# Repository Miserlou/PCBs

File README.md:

# Black Death PCBs

Kosmo circuits/panels by me. Mostly hacks of other people's work.

USE THESE AT YOUR OWN RISK, SOME HAVE MAJOR BUGS! You probably want to talk to me before making these.

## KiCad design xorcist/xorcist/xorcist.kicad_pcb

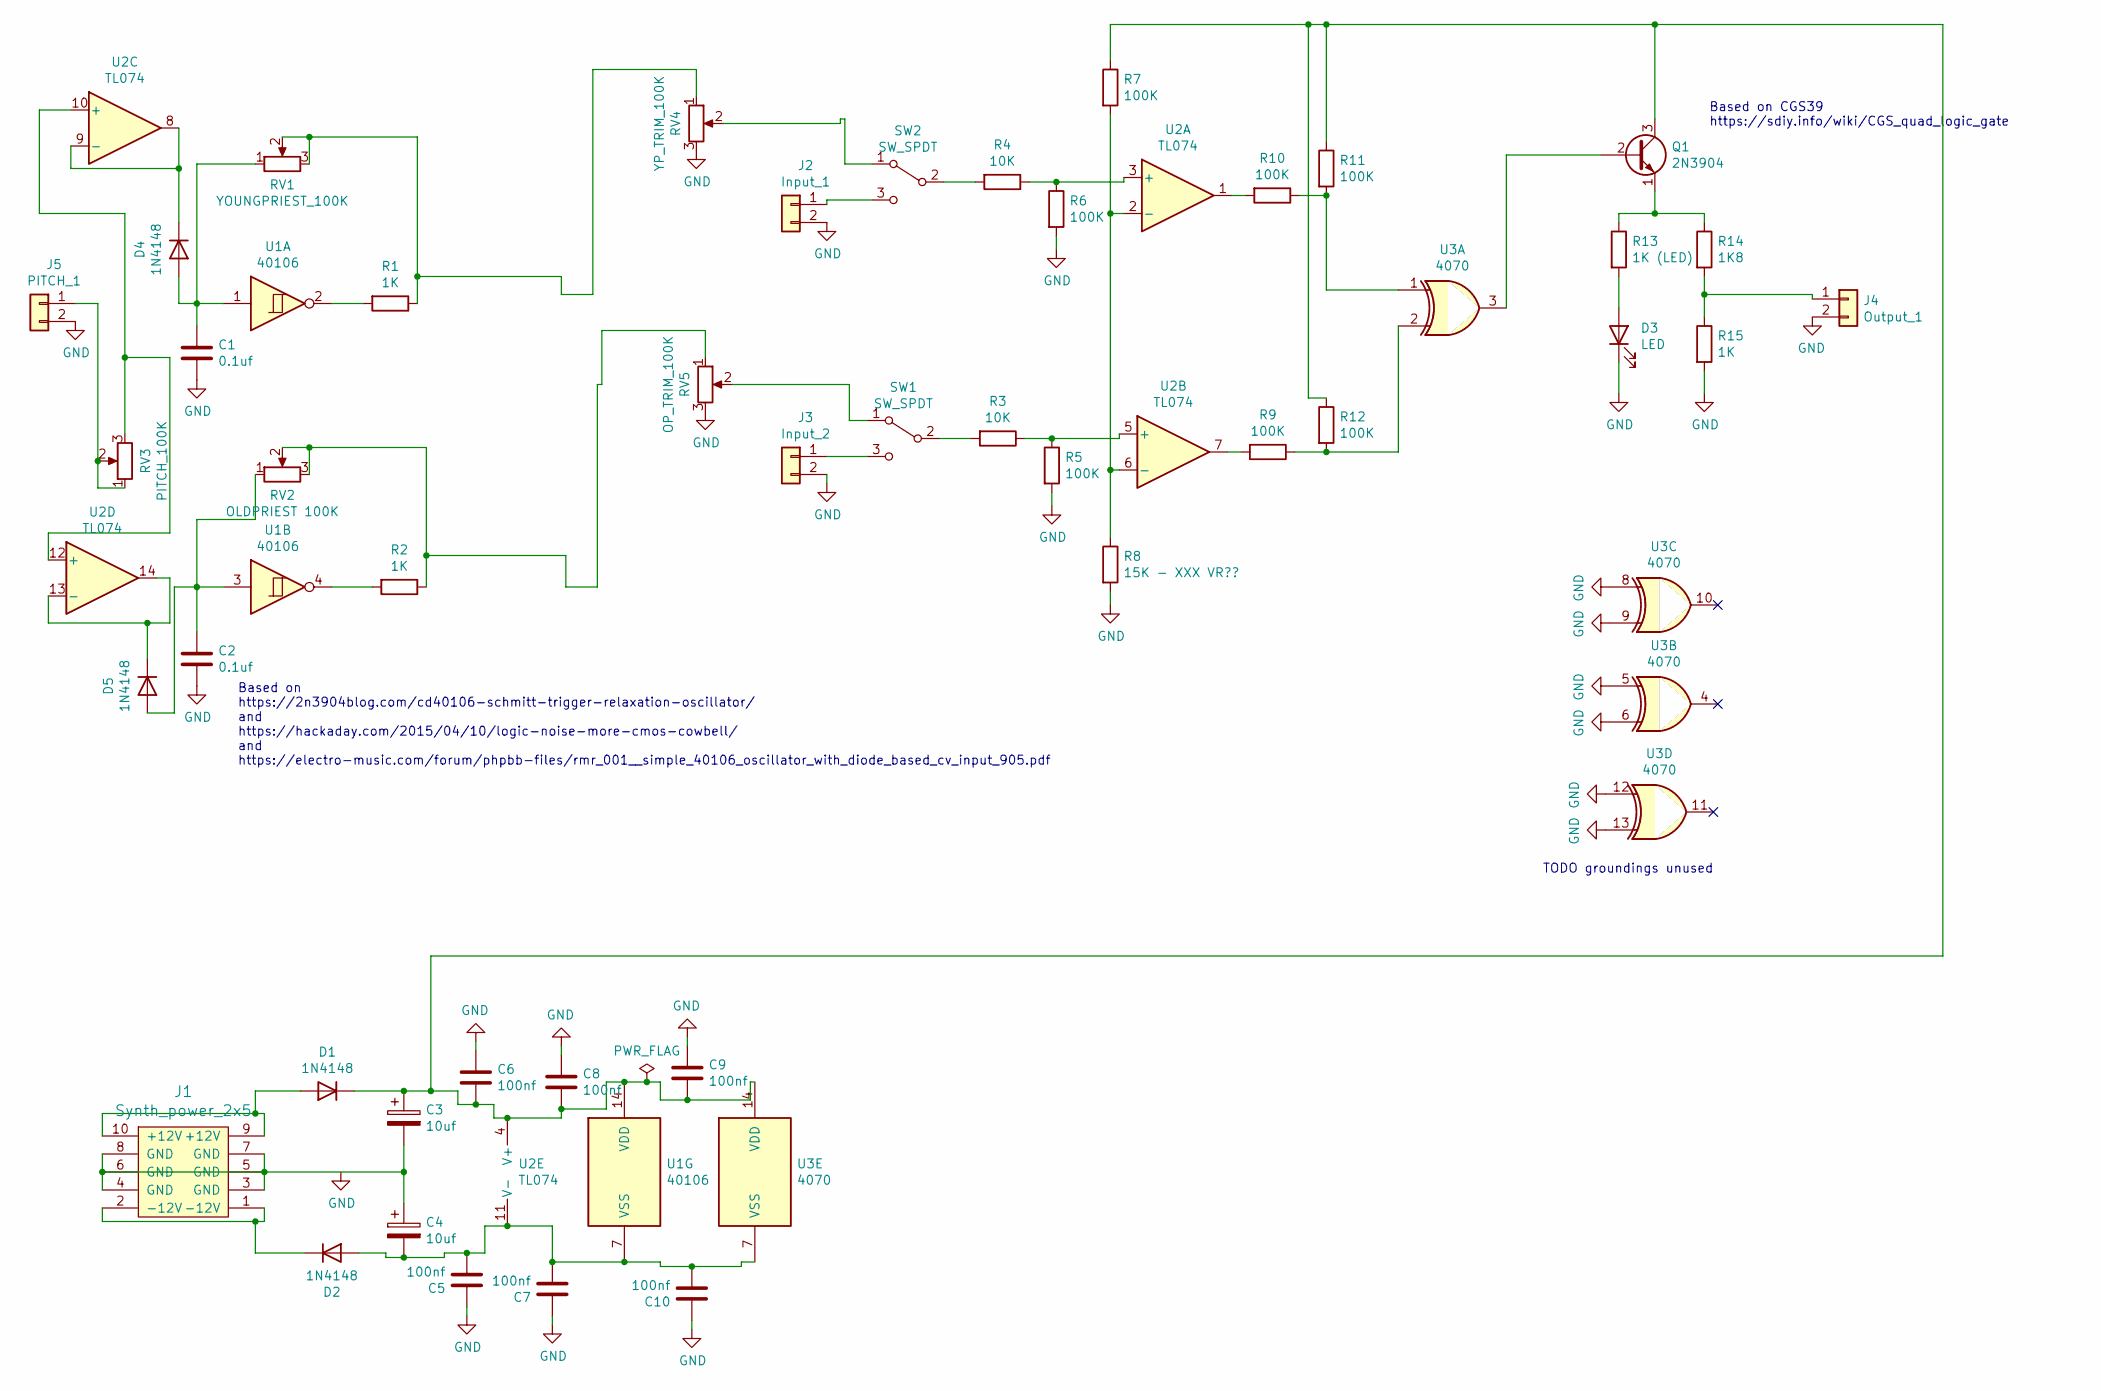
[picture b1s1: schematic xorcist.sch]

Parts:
C1, C2: 0.1uf; C_Disc_D3.0mm_W1.6mm_P2.50mm
C3, C4: 10uf; CP_Radial_D6.3mm_P2.50mm
C5, C6, C7, C8, C9, C10: 100nf; C_Disc_D3.0mm_W1.6mm_P2.50mm
D1, D2, D4, D5: 1N4148; D_DO-35_SOD27_P7.62mm_Horizontal
D3: LED; LED_D5.0mm
J1: Synth_power_2x5; Power_Header
J2: Input_1; Molex_KK-254_AE-6410-02A_1x02_P2.54mm_Vertical
J3: Input_2; Molex_KK-254_AE-6410-02A_1x02_P2.54mm_Vertical
J4: Output_1; Molex_KK-254_AE-6410-02A_1x02_P2.54mm_Vertical
J5: PITCH_1; Molex_KK-254_AE-6410-02A_1x02_P2.54mm_Vertical
Q1: 2N3904; TO-92_Inline_Wide
R1, R2, R15: 1K; R_Axial_DIN0207_L6.3mm_D2.5mm_P10.16mm_Horizontal
R3, R4: 10K; R_Axial_DIN0207_L6.3mm_D2.5mm_P10.16mm_Horizontal
R5, R6, R7, R9, R10, R11, R12: 100K; R_Axial_DIN0207_L6.3mm_D2.5mm_P10.16mm_Horizontal
R8: 15K - XXX VR??; R_Axial_DIN0207_L6.3mm_D2.5mm_P10.16mm_Horizontal
R13: 1K (LED); R_Axial_DIN0207_L6.3mm_D2.5mm_P10.16mm_Horizontal
R14: 1K8; R_Axial_DIN0207_L6.3mm_D2.5mm_P10.16mm_Horizontal
RV1: YOUNGPRIEST_100K; Potentiometer_Alpha_RD901F-40-00D_Single_Vertical_CircularH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
RV2: OLDPRIEST 100K; Potentiometer_Alpha_RD901F-40-00D_Single_Vertical_CircularH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
RV3: PITCH_100K; Potentiometer_Alpha_RD901F-40-00D_Single_Vertical_CircularH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
RV4: YP_TRIM_100K; Potentiometer_Bourns_3296W_Vertical_standard
RV5: OP_TRIM_100K; Potentiometer_Bourns_3296W_Vertical_standard
SW1, SW2: SW_SPDT; SPDT-toggle-switch-1M-series
U1: 40106; DIP-14_W7.62mm_Socket_LongPads
U2: TL074; DIP-16_W7.62mm_Socket_LongPads
U3: 4070; DIP-14_W7.62mm_Socket_LongPads

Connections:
unnamed: C1.1, D4.2 (A), RV1.1, U1.1
unnamed: C2.1, D5.2 (A), RV2.1, U1.3
unnamed: C3.1, C6.2, C8.2, C9.2, D1.1 (K), Q1.3 (C), R7.1, R11.1, R12.1, U1.14 (VDD), U2.4 (V+), U3.14 (VDD)
unnamed: C4.2, C5.2, C7.2, C10.2, D2.2 (A), U1.7 (VSS), U2.11 (V-), U3.7 (VSS)
unnamed: D1.2 (A), J1.9 (+12V), J1.10 (+12V)
unnamed: D2.1 (K), J1.1 (-12V), J1.2 (-12V)
unnamed: D3.2 (A), R13.2
unnamed: D4.1 (K), U2.8, U2.9 (-)
unnamed: D5.1 (K), U2.13 (-), U2.14
unnamed 9: J2.1, SW2.3 (C); also elsewhere on the board
unnamed 10: J3.1, SW1.3 (C); also elsewhere on the board
unnamed 11: J4.1, R14.2, R15.1; also elsewhere on the board
unnamed 12: J5.1, RV3.1, RV3.2; also elsewhere on the board
unnamed: Q1.1 (E), R13.1, R14.1
unnamed: Q1.2 (B), U3.3
unnamed: R1.1, RV1.2, RV1.3, RV4.1
unnamed: R1.2, U1.2
unnamed: R2.1, RV2.2, RV2.3, RV5.1
unnamed: R2.2, U1.4
unnamed: R3.1, R5.1, U2.5 (+)
unnamed: R3.2, SW1.2 (B)
unnamed: R4.1, R6.1, U2.3 (+)
unnamed: R4.2, SW2.2 (B)
unnamed: R7.2, R8.1, U2.2 (-), U2.6 (-)
unnamed: R9.2, U2.7
unnamed: R10.1, R11.2, U3.1
unnamed: R10.2, U2.1
unnamed: R9.1, R12.2, U3.2
unnamed: RV3.3, U2.10 (+), U2.12 (+)
unnamed: RV4.2, SW2.1 (A)
unnamed: RV5.2, SW1.1 (A)

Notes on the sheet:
Based on CGS39 https://sdiy.info/wiki/CGS_quad_logic_gate
Based on https://2n3904blog.com/cd40106-schmitt-trigger-relaxation-oscillator/ and https://hackaday.com/2015/04/10/logic-noise-more-cmos-cowbell/ and https://electro-music.com/forum/phpbb-files/rmr_001__simple_40106_oscillator_with_diode_based_cv_input_905.pdf
TODO groundings unused

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
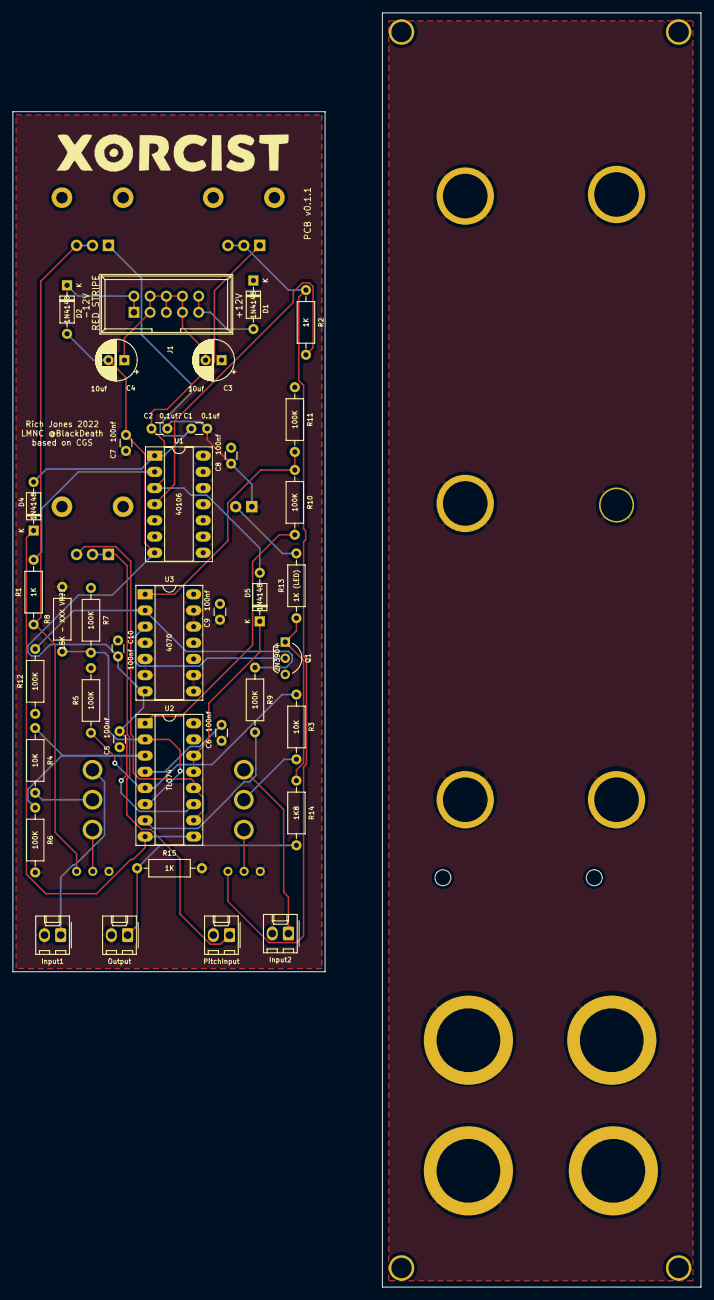
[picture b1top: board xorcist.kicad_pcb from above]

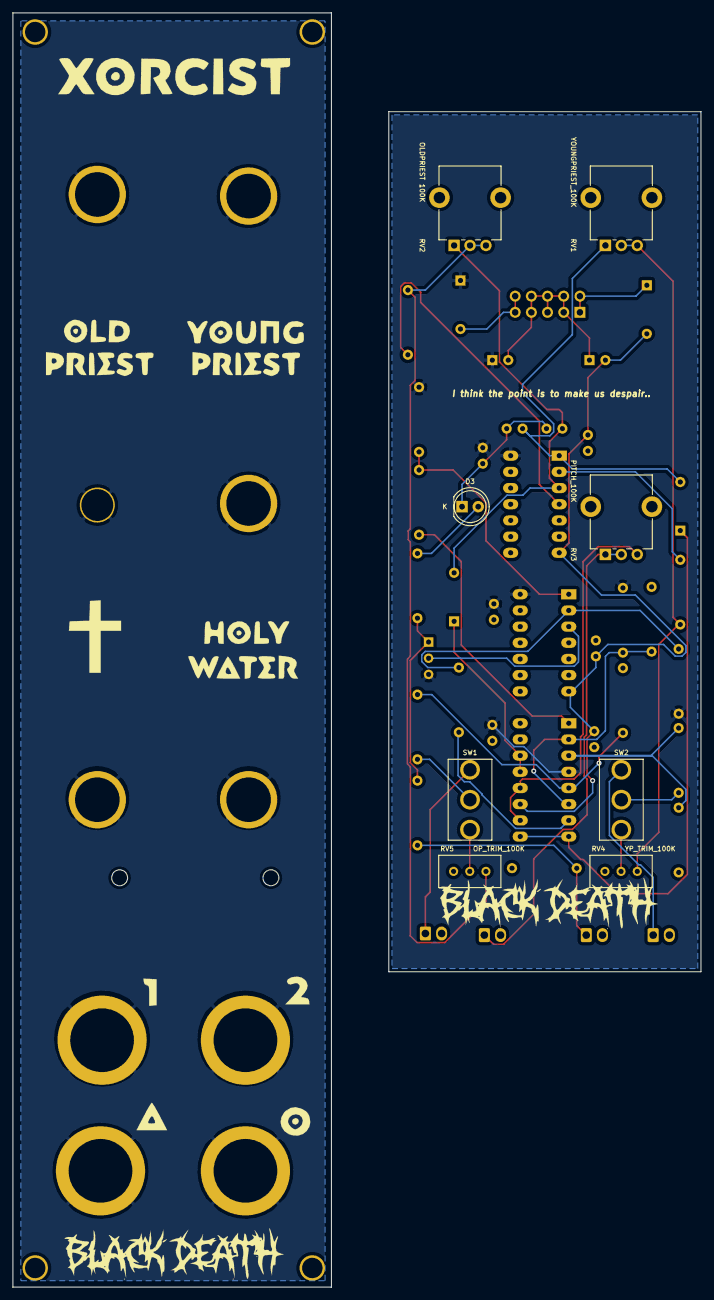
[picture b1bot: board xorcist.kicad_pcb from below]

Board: 2 copper layers, 108.0 x 200.0 mm, 46 parts (8 on the bottom side), 33 nets.

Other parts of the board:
Input1: Input_1; Molex_KK-254_AE-6410-02A_1x02_P2.54mm_Vertical
Input2: Input_2; Molex_KK-254_AE-6410-02A_1x02_P2.54mm_Vertical
Output: Output_1; Molex_KK-254_AE-6410-02A_1x02_P2.54mm_Vertical
PitchInput: PITCH_1; Molex_KK-254_AE-6410-02A_1x02_P2.54mm_Vertical

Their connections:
unnamed 9: Input1.1; also elsewhere on the board
unnamed 10: Input2.1; also elsewhere on the board
unnamed 11: Output.1; also elsewhere on the board
unnamed 12: PitchInput.1; also elsewhere on the board

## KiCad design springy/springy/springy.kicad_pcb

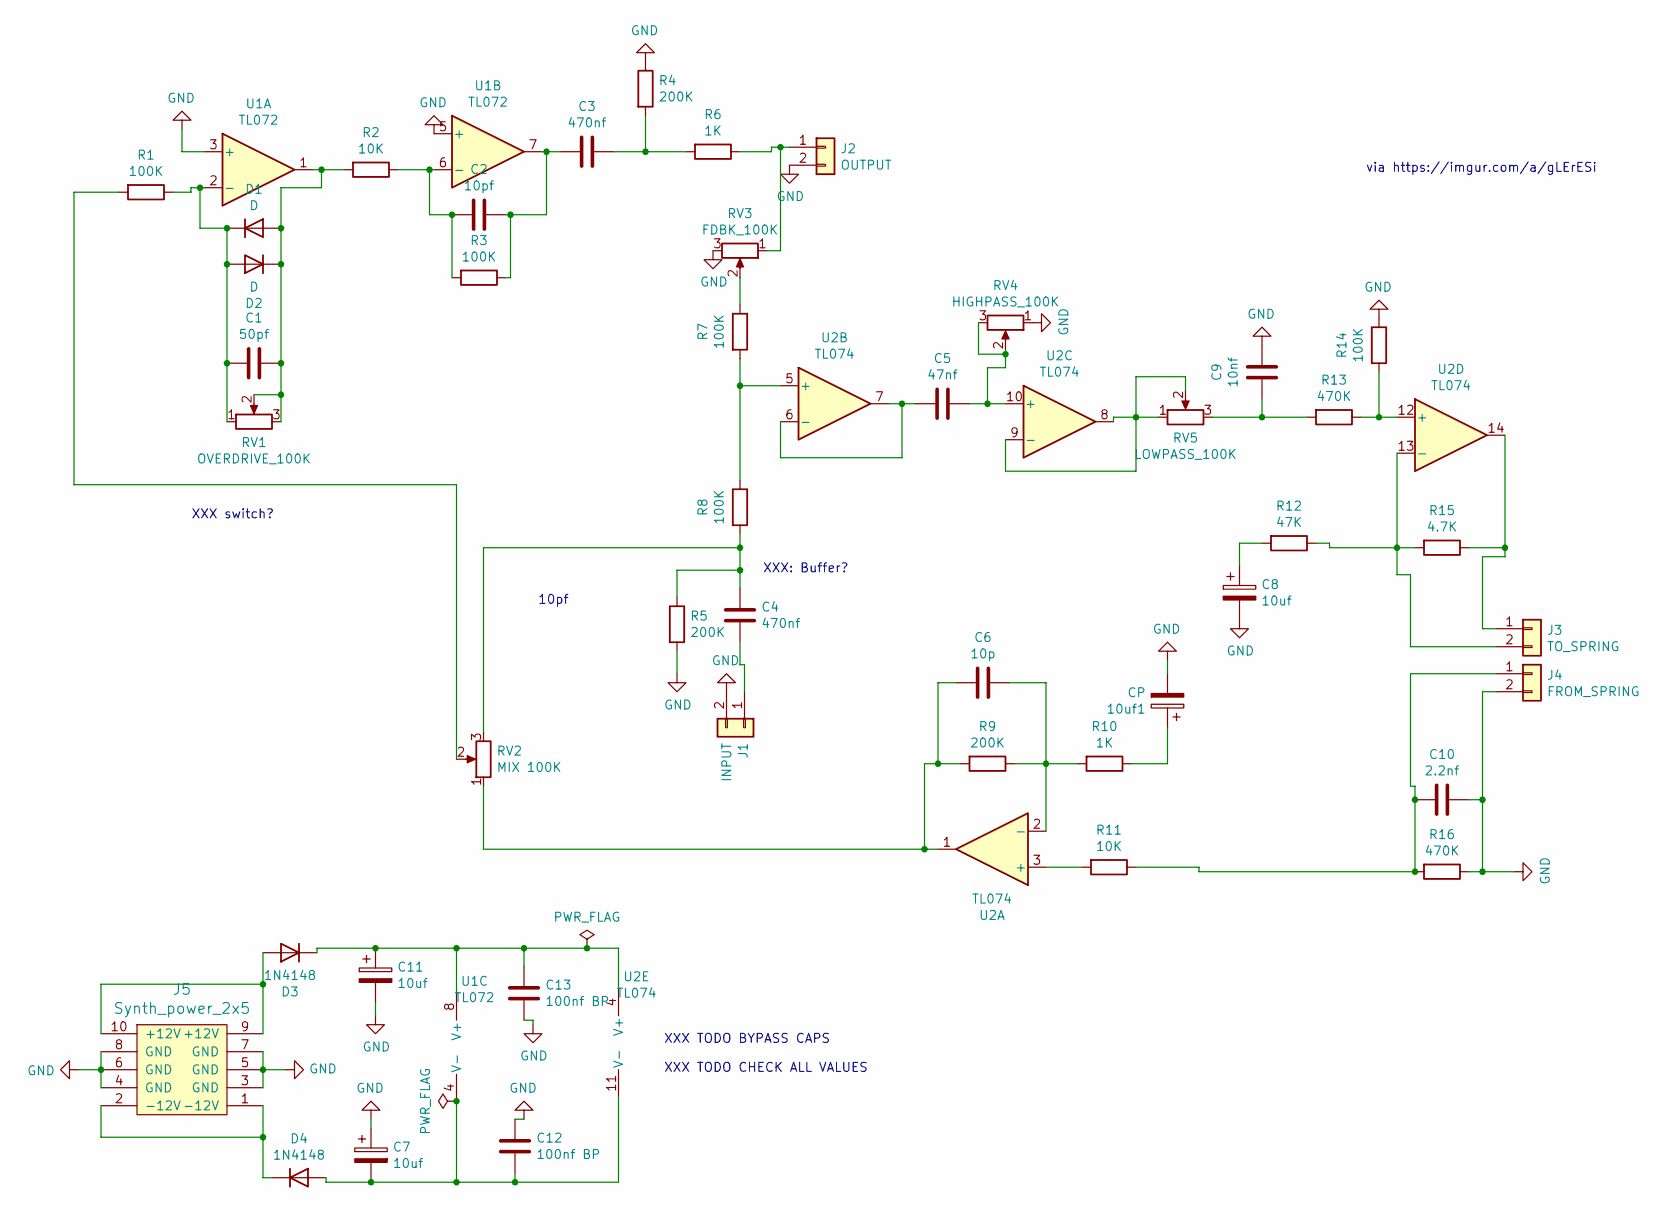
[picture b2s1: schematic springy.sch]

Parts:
10uf1: CP; CP_Radial_D6.3mm_P2.50mm
C1: 50pf; C_Disc_D3.0mm_W1.6mm_P2.50mm
C2: 10pf; C_Disc_D3.0mm_W1.6mm_P2.50mm
C3, C4: 470nf; C_Disc_D3.0mm_W1.6mm_P2.50mm
C5: 47nf; C_Disc_D3.0mm_W1.6mm_P2.50mm
C6: 10p; C_Disc_D3.0mm_W1.6mm_P2.50mm
C7, C8, C11: 10uf; CP_Radial_D6.3mm_P2.50mm
C9: 10nf; C_Disc_D3.0mm_W1.6mm_P2.50mm
C10: 2.2nf; C_Disc_D3.0mm_W1.6mm_P2.50mm
C12, C13: 100nf BP; C_Disc_D3.0mm_W1.6mm_P2.50mm
D1, D2: D; D_DO-41_SOD81_P7.62mm_Horizontal
D3, D4: 1N4148; D_DO-35_SOD27_P7.62mm_Horizontal
J1: INPUT; Molex_KK-254_AE-6410-02A_1x02_P2.54mm_Vertical
J2: OUTPUT; Molex_KK-254_AE-6410-02A_1x02_P2.54mm_Vertical
J3: TO_SPRING; Molex_KK-254_AE-6410-02A_1x02_P2.54mm_Vertical
J4: FROM_SPRING; Molex_KK-254_AE-6410-02A_1x02_P2.54mm_Vertical
J5: Synth_power_2x5; Power_Header
R1, R3, R7, R8, R14: 100K; R_Axial_DIN0207_L6.3mm_D2.5mm_P10.16mm_Horizontal
R2, R11: 10K; R_Axial_DIN0207_L6.3mm_D2.5mm_P10.16mm_Horizontal
R4, R5, R9: 200K; R_Axial_DIN0207_L6.3mm_D2.5mm_P10.16mm_Horizontal
R6, R10: 1K; R_Axial_DIN0207_L6.3mm_D2.5mm_P10.16mm_Horizontal
R12: 47K; R_Axial_DIN0207_L6.3mm_D2.5mm_P10.16mm_Horizontal
R13, R16: 470K; R_Axial_DIN0207_L6.3mm_D2.5mm_P10.16mm_Horizontal
R15: 4.7K; R_Axial_DIN0207_L6.3mm_D2.5mm_P10.16mm_Horizontal
RV1: OVERDRIVE_100K; Potentiometer_Alpha_RD901F-40-00D_Single_Vertical_CircularH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
RV2: MIX 100K; Potentiometer_Alpha_RD901F-40-00D_Single_Vertical_CircularH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
RV3: FDBK_100K; Potentiometer_Alpha_RD901F-40-00D_Single_Vertical_CircularH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
RV4: HIGHPASS_100K; Potentiometer_Alpha_RD901F-40-00D_Single_Vertical_CircularH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
RV5: LOWPASS_100K; Potentiometer_Alpha_RD901F-40-00D_Single_Vertical_CircularH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
U1: TL072; DIP-8_W7.62mm_Socket_LongPads
U2: TL074; DIP-16_W7.62mm_Socket_LongPads

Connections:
GND: 10uf1.2, C7.1, C8.2, C9.2, C10.2, C11.2, C12.1, C13.2, J1.2, J2.2, J4.2, J5.3 (GND), J5.4 (GND), J5.5 (GND), J5.6 (GND), J5.7 (GND), J5.8 (GND), R4.1, R5.2, R14.1, R16.1, RV3.3, RV4.1, U1.3 (+), U1.5 (+); also elsewhere on the board
unnamed: 10uf1.1, R10.1
unnamed: C1.1, D1.1 (K), D2.2 (A), R1.1, RV1.1, U1.2 (-)
unnamed: C1.2, D1.2 (A), D2.1 (K), R2.2, RV1.2, RV1.3, U1.1
unnamed: C2.1, R2.1, R3.2, U1.6 (-)
unnamed: C2.2, C3.1, R3.1, U1.7
unnamed: C3.2, R4.2, R6.2
unnamed: C4.1, R5.1, R8.2, RV2.3
unnamed 8: C4.2, J1.1; also elsewhere on the board
unnamed: C5.1, U2.6 (-), U2.7
unnamed: C5.2, RV4.2, RV4.3, U2.10 (+)
unnamed: C6.1, R9.2, RV2.1, U2.1
unnamed: C6.2, R9.1, R10.2, U2.2 (-)
unnamed: C8.1, R12.2
unnamed: C9.1, R13.2, RV5.3
unnamed 15: C10.1, J4.1, R11.1, R16.2; also elsewhere on the board
unnamed: C11.1, C13.1, D3.1 (K), U1.8 (V+), U2.4 (V+)
unnamed: C7.2, C12.2, D4.2 (A), U1.4 (V-), U2.11 (V-)
unnamed: D3.2 (A), J5.9 (+12V), J5.10 (+12V)
unnamed: D4.1 (K), J5.1 (-12V), J5.2 (-12V)
unnamed 20: J2.1, R6.1, RV3.1; also elsewhere on the board
unnamed 21: J3.1, R15.1, U2.14; also elsewhere on the board
unnamed 22: J3.2, R12.1, R15.2, U2.13 (-); also elsewhere on the board
unnamed: R1.2, RV2.2
unnamed: R7.1, RV3.2
unnamed: R7.2, R8.1, U2.5 (+)
unnamed: R11.2, U2.3 (+)
unnamed: R13.1, R14.2, U2.12 (+)
unnamed: RV5.1, RV5.2, U2.8, U2.9 (-)

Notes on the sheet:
XXX: Buffer?
via https://imgur.com/a/gLErESi
10pf
XXX TODO BYPASS CAPS XXX TODO CHECK ALL VALUES
XXX switch?

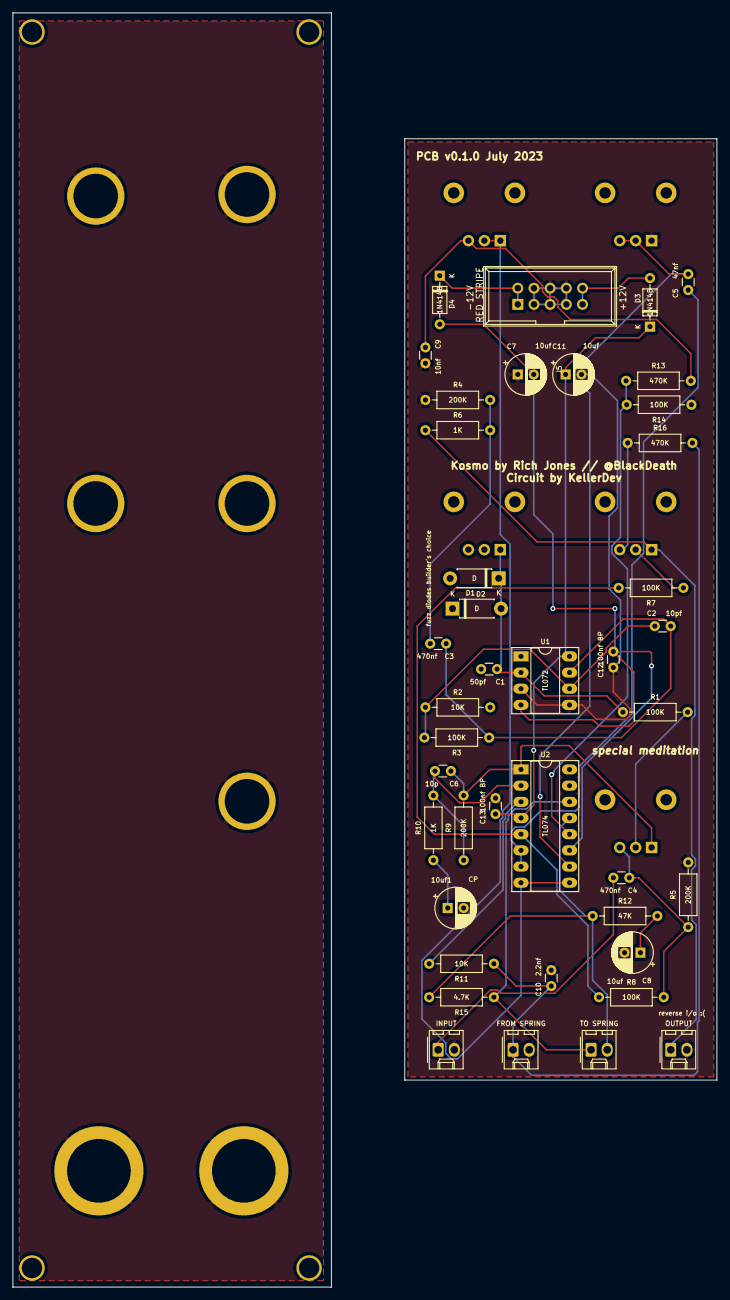
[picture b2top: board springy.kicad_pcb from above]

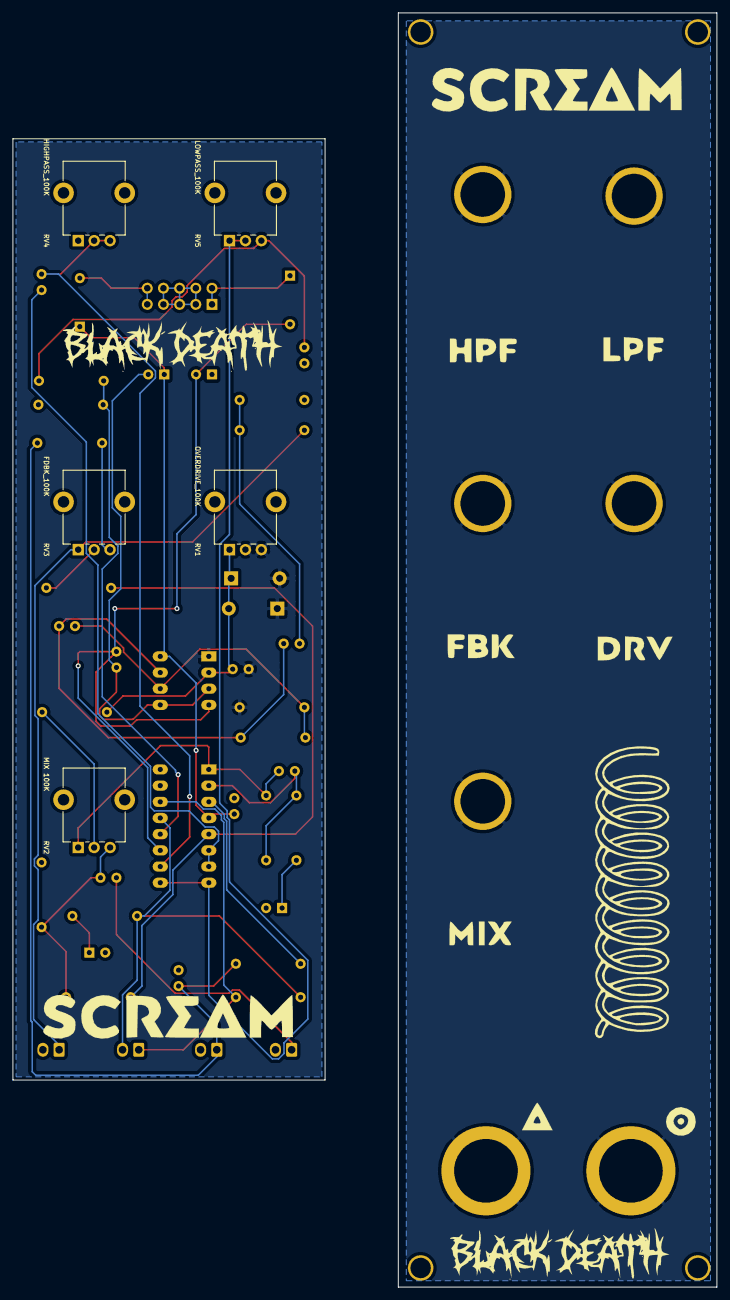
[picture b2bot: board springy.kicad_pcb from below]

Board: 2 copper layers, 110.5 x 200.0 mm, 46 parts (5 on the bottom side), 29 nets.

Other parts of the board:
FROM SPRING: FROM_SPRING; Molex_KK-254_AE-6410-02A_1x02_P2.54mm_Vertical
INPUT: INPUT; Molex_KK-254_AE-6410-02A_1x02_P2.54mm_Vertical
OUTPUT: OUTPUT; Molex_KK-254_AE-6410-02A_1x02_P2.54mm_Vertical
TO SPRING: TO_SPRING; Molex_KK-254_AE-6410-02A_1x02_P2.54mm_Vertical

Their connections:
GND: FROM SPRING.2, INPUT.2, OUTPUT.2; also elsewhere on the board
unnamed 8: INPUT.1; also elsewhere on the board
unnamed 15: FROM SPRING.1; also elsewhere on the board
unnamed 20: OUTPUT.1; also elsewhere on the board
unnamed 21: TO SPRING.1; also elsewhere on the board
unnamed 22: TO SPRING.2; also elsewhere on the board

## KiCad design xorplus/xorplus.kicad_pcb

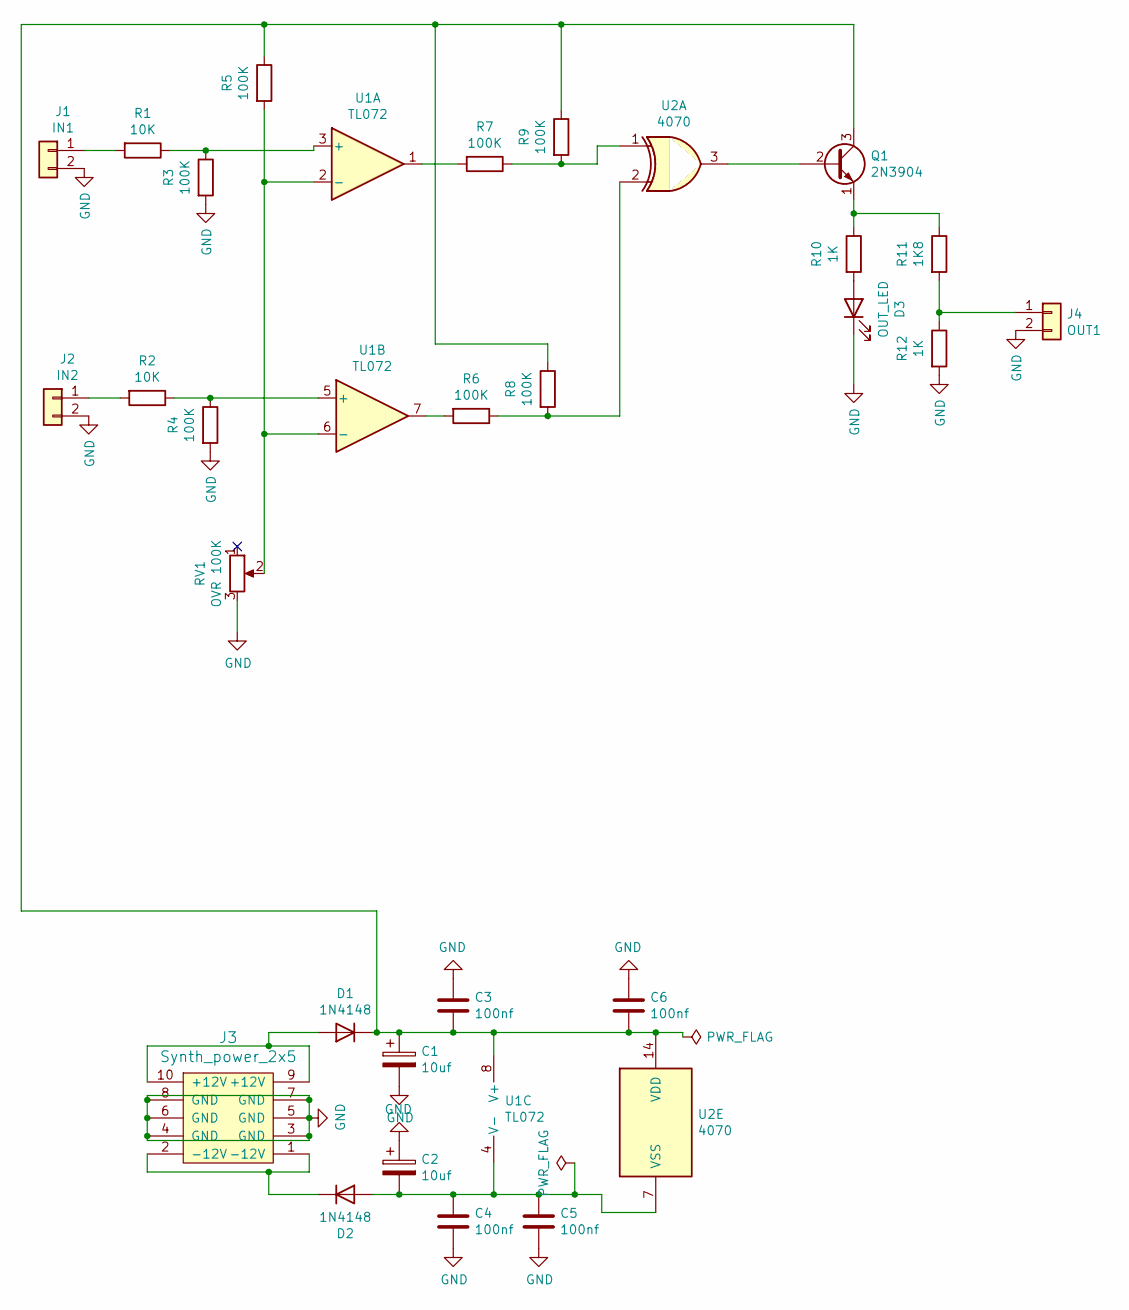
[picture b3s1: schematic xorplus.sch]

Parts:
C1, C2: 10uf; CP_Radial_D5.0mm_P2.00mm
C3, C4, C5, C6: 100nf; C_Rect_L7.2mm_W2.5mm_P5.00mm_FKS2_FKP2_MKS2_MKP2
D1, D2: 1N4148; D_DO-35_SOD27_P7.62mm_Horizontal
D3: OUT_LED; LED_D5.0mm
J1: IN1; Molex_KK-254_AE-6410-02A_1x02_P2.54mm_Vertical
J2: IN2; Molex_KK-254_AE-6410-02A_1x02_P2.54mm_Vertical
J3: Synth_power_2x5; Power_Header
J4: OUT1; Molex_KK-254_AE-6410-02A_1x02_P2.54mm_Vertical
Q1: 2N3904; TO-92_Inline
R1, R2: 10K; R_Axial_DIN0207_L6.3mm_D2.5mm_P7.62mm_Horizontal
R3, R4, R5, R6, R7, R8, R9: 100K; R_Axial_DIN0207_L6.3mm_D2.5mm_P7.62mm_Horizontal
R10, R12: 1K; R_Axial_DIN0207_L6.3mm_D2.5mm_P7.62mm_Horizontal
R11: 1K8; R_Axial_DIN0207_L6.3mm_D2.5mm_P7.62mm_Horizontal
RV1: OVR 100K; Potentiometer_Alpha_RD901F-40-00D_Single_Vertical_CircularH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
U1: TL072; DIP-8_W7.62mm_Socket_LongPads
U2: 4070; DIP-14_W7.62mm_Socket_LongPads

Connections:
GND: C1.2, C2.1, C3.1, C4.2, C5.2, C6.1, D3.1 (K), J1.2, J2.2, J3.3 (GND), J3.4 (GND), J3.5 (GND), J3.6 (GND), J3.7 (GND), J3.8 (GND), J4.2, R3.2, R4.2, R12.2, RV1.3
unnamed: C1.1, C3.2, C6.2, D1.1 (K), Q1.3 (C), R5.1, R8.1, R9.1, U1.8 (V+), U2.14 (VDD)
unnamed: C2.2, C4.1, C5.1, D2.2 (A), U1.4 (V-), U2.7 (VSS)
unnamed: D1.2 (A), J3.9 (+12V), J3.10 (+12V)
unnamed: D2.1 (K), J3.1 (-12V), J3.2 (-12V)
unnamed: D3.2 (A), R10.2
unnamed: J1.1, R1.2
unnamed: J2.1, R2.2
unnamed: J4.1, R11.2, R12.1
unnamed: Q1.1 (E), R10.1, R11.1
unnamed: Q1.2 (B), U2.3
unnamed: R1.1, R3.1, U1.3 (+)
unnamed: R2.1, R4.1, U1.5 (+)
unnamed: R5.2, RV1.2, U1.2 (-), U1.6 (-)
unnamed: R6.1, R8.2, U2.2
unnamed: R6.2, U1.7
unnamed: R7.1, R9.2, U2.1
unnamed: R7.2, U1.1

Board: 2 copper layers, 29 parts (2 on the bottom side), 18 nets, no tracks yet.

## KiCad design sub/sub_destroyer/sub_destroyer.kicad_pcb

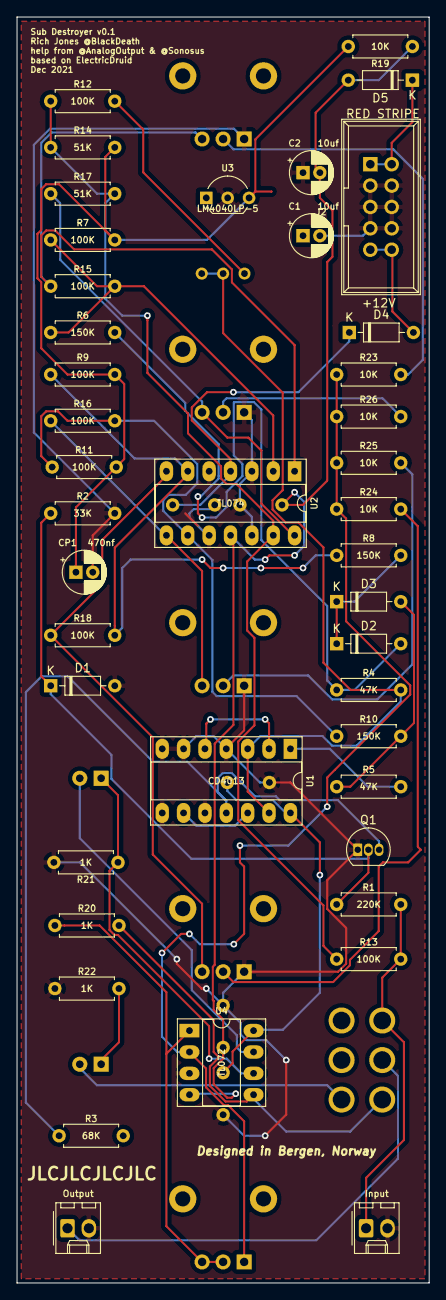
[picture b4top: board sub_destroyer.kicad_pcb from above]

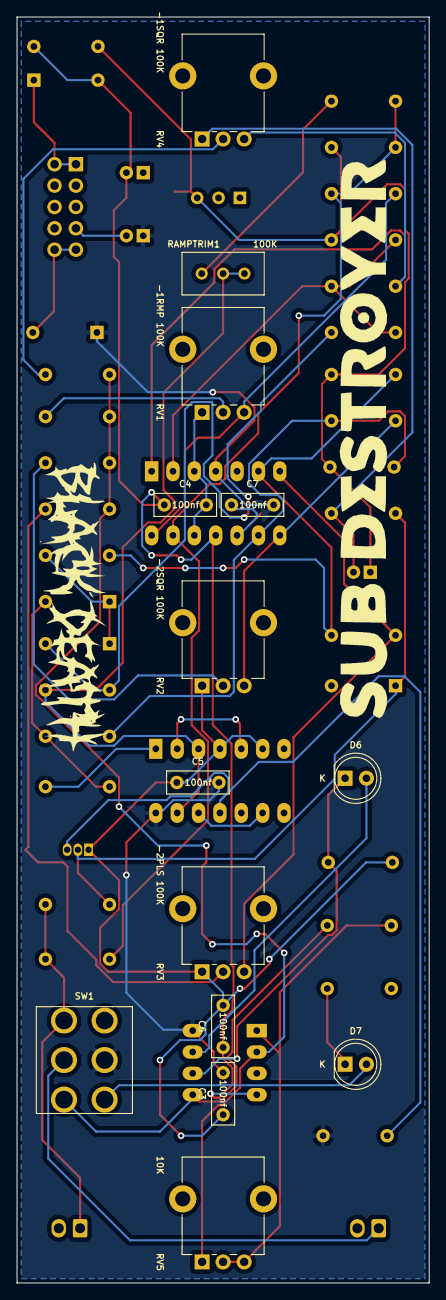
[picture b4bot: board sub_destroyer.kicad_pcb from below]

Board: 2 copper layers, 49.0 x 150.5 mm, 56 parts (14 on the bottom side), 37 nets.

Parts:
C1, C2: 10uf; CP_Radial_D5.0mm_P2.00mm
C3, C4, C5, C6, C7: 100nf; C_Rect_L7.2mm_W2.5mm_P5.00mm_FKS2_FKP2_MKS2_MKP2
CP1: 470nf; CP_Radial_D5.0mm_P2.00mm
D1, D2, D3, D4, D5: 1N4148; D_DO-35_SOD27_P7.62mm_Horizontal
D6: SIG_LED; LED_D5.0mm
D7: PWR_LED; LED_D5.0mm
Input: INPUT; Molex_KK-254_AE-6410-02A_1x02_P2.54mm_Vertical
J2: Synth_power_2x5; Power_Header
Output: OUTPUT; Molex_KK-254_AE-6410-02A_1x02_P2.54mm_Vertical
Q1: 2N3904; TO-92_Inline
R1: 220K; R_Axial_DIN0207_L6.3mm_D2.5mm_P7.62mm_Horizontal
R2: 33K; R_Axial_DIN0207_L6.3mm_D2.5mm_P7.62mm_Horizontal
R3: 68K; R_Axial_DIN0207_L6.3mm_D2.5mm_P7.62mm_Horizontal
R4, R5: 47K; R_Axial_DIN0207_L6.3mm_D2.5mm_P7.62mm_Horizontal
R6, R8, R10: 150K; R_Axial_DIN0207_L6.3mm_D2.5mm_P7.62mm_Horizontal
R7, R9, R11, R12, R13, R15, R16, R18: 100K; R_Axial_DIN0207_L6.3mm_D2.5mm_P7.62mm_Horizontal
R14, R17: 51K; R_Axial_DIN0207_L6.3mm_D2.5mm_P7.62mm_Horizontal
R19, R23, R24, R25, R26: 10K; R_Axial_DIN0207_L6.3mm_D2.5mm_P7.62mm_Horizontal
R20, R21, R22: 1K; R_Axial_DIN0207_L6.3mm_D2.5mm_P7.62mm_Horizontal
RAMPTRIM1: 100K; Potentiometer_Bourns_3296W_Vertical
RV1: -1RMP 100K; Potentiometer_Alpha_RD901F-40-00D_Single_Vertical_CircularH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
RV2: -2SQR 100K; Potentiometer_Alpha_RD901F-40-00D_Single_Vertical_CircularH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
RV3: -2PLS 100K; Potentiometer_Alpha_RD901F-40-00D_Single_Vertical_CircularH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
RV4: -1SQR 100K; Potentiometer_Alpha_RD901F-40-00D_Single_Vertical_CircularH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
RV5: 10K; Potentiometer_Alpha_RD901F-40-00D_Single_Vertical_CircularH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
SW1: ONOFF_SW; DPDT-toggle-switch-1M-seriesx
U1: CD4013; DIP-14_W7.62mm_Socket_LongPads
U2: TL074; DIP-14_W7.62mm_Socket_LongPads
U3: LM4040LP-5; TO-92_Inline_Wide
U4: TL072; DIP-8_W7.62mm_Socket_LongPads

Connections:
GND: C1.2, C2.1, C3.1, C4.2, C5.1, C6.2, C7.1, CP1.2, D1.2, Input.2, J2.3, J2.4, J2.5, J2.6, J2.7, J2.8, Output.2, Q1.1, R2.2, R21.2, R22.1, RV1.1, RV2.1, RV3.1, RV4.1, U1.4, U1.6, U1.7, U1.8, U1.10, U2.3, U2.5, U2.10, U2.12, U3.2, U4.3
unnamed: C1.1, C3.2, C5.2, C7.2, D4.1, R3.2, SW1.2, U1.14, U2.4, U4.8
unnamed: C2.2, C4.1, C6.1, D5.2, R19.1, U2.11, U4.4
unnamed: CP1.1, R7.2, R9.2, R11.2, R14.2, R19.2, U3.3
unnamed: D1.1, Q1.2, R1.1, R2.1
unnamed: D2.1, D3.1, R8.2
unnamed: D2.2, R4.1, R6.2
unnamed: D3.2, R5.1, R10.2
unnamed: D4.2, J2.9, J2.10
unnamed: D5.1, J2.1, J2.2
unnamed: D6.1, R21.1, U4.6
unnamed: D6.2, U4.7
unnamed: D7.1, R22.2
unnamed: D7.2, SW1.1
unnamed: Input.1, R1.2, R13.2, SW1.6
unnamed: Output.1, SW1.5
unnamed: Q1.3, R3.1, U1.11
unnamed: R4.2, RAMPTRIM1.1, RAMPTRIM1.2, U1.3, U1.13
unnamed: R5.2, U1.1
unnamed: R10.1, R11.1, R16.2, U2.9
unnamed: R12.1, R13.1, R14.1, R17.2, U2.13
unnamed: R12.2, RAMPTRIM1.3
unnamed: R15.1, RV4.3, U2.1
unnamed: R6.1, R7.1, R15.2, U2.2
unnamed: R16.1, RV2.3, U2.8
unnamed: R17.1, RV1.3, U2.14
unnamed: R18.1, RV3.3, U2.7
unnamed: R8.1, R9.1, R18.2, U2.6
unnamed: R20.1, RV5.2, RV5.3, U4.1
unnamed: R20.2, SW1.4, U4.5
unnamed: R23.1, R24.1, R25.1, R26.1, RV5.1, U4.2
unnamed: R23.2, RV4.2
unnamed: R24.2, RV3.2
unnamed: R25.2, RV2.2
unnamed: R26.2, RV1.2
unnamed: U1.2, U1.5
unnamed: U1.9, U1.12

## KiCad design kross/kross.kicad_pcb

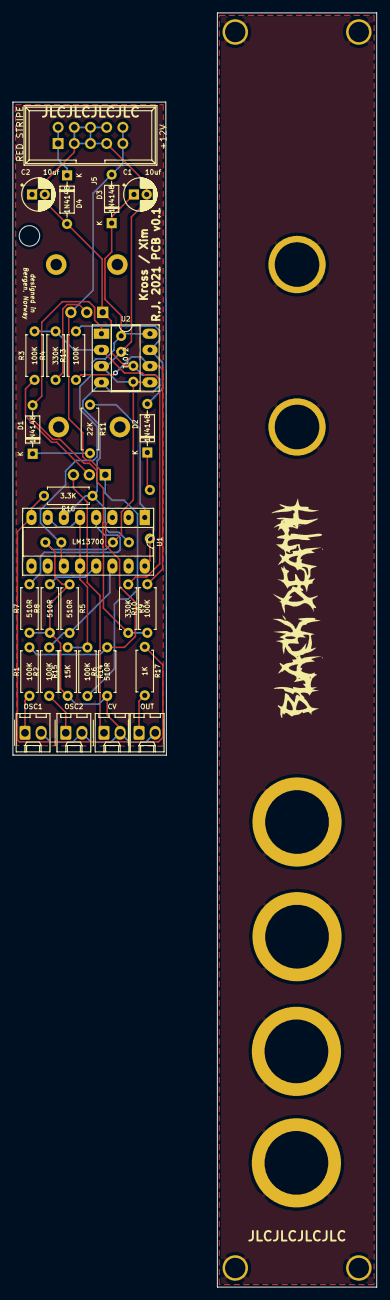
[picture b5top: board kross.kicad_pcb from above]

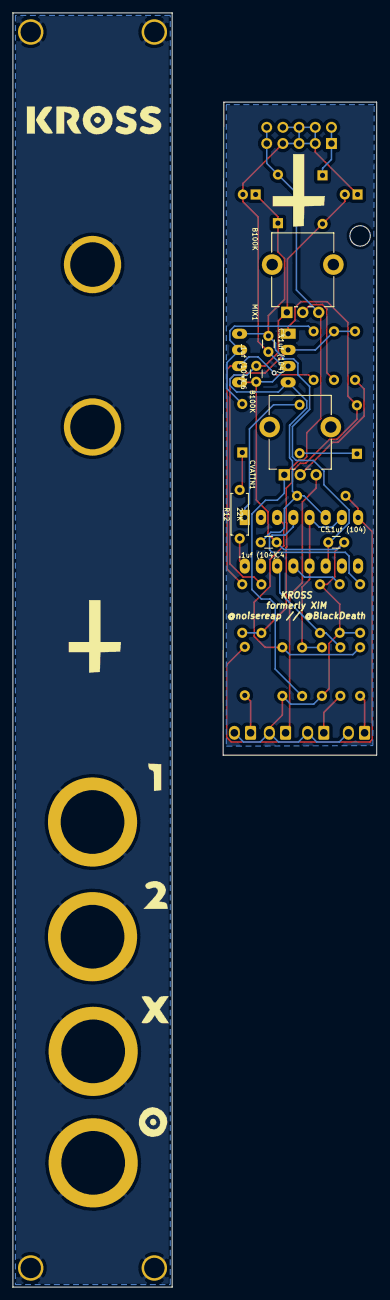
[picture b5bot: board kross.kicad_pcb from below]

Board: 2 copper layers, 57.1 x 200.0 mm, 37 parts (7 on the bottom side), 25 nets.

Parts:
C1, C2: 10uf; CP_Radial_D5.0mm_P2.00mm
C3, C4, C5, C6: .1uf (104); C_Disc_D3.0mm_W1.6mm_P2.50mm
CV: CV; Molex_KK-254_AE-6410-02A_1x02_P2.54mm_Vertical
CVATTN1: B100K; Potentiometer_Alpha_RD901F-40-00D_Single_Vertical_CircularH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
D1, D2, D3, D4: 1N4148; D_DO-35_SOD27_P7.62mm_Horizontal
H2: MountingHole; MountingHole_3.2mm_M3
J5: Synth_power_2x5; Power_Header
MIX1: B100K; Potentiometer_Alpha_RD901F-40-00D_Single_Vertical_CircularH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
OSC1: OSC1; Molex_KK-254_AE-6410-02A_1x02_P2.54mm_Vertical
OSC2: OSC2; Molex_KK-254_AE-6410-02A_1x02_P2.54mm_Vertical
OUT: OUT; Molex_KK-254_AE-6410-02A_1x02_P2.54mm_Vertical
R1, R2, R3, R10, R13, R14: 100K; R_Axial_DIN0207_L6.3mm_D2.5mm_P7.62mm_Horizontal
R4, R9: 330K; R_Axial_DIN0207_L6.3mm_D2.5mm_P7.62mm_Horizontal
R5, R6, R7, R8: 510R; R_Axial_DIN0207_L6.3mm_D2.5mm_P7.62mm_Horizontal
R11, R12: 22K; R_Axial_DIN0207_L6.3mm_D2.5mm_P7.62mm_Horizontal
R15: 15K; R_Axial_DIN0207_L6.3mm_D2.5mm_P7.62mm_Horizontal
R16: 3.3K; R_Axial_DIN0207_L6.3mm_D2.5mm_P7.62mm_Horizontal
R17: 1K; R_Axial_DIN0207_L6.3mm_D2.5mm_P7.62mm_Horizontal
U1: LM13700; DIP-16_W7.62mm_Socket_LongPads
U2: TL072; DIP-8_W7.62mm_Socket_LongPads

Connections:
GND: C1.2, C2.1, C3.2, C4.1, C5.2, C6.1, CV.2, J5.3, J5.4, J5.5, J5.6, J5.7, J5.8, OSC1.2, OSC2.2, OUT.2, R5.1, R6.1, R7.1, R8.1, R15.1, U2.3, U2.5
unnamed: C1.1, C3.1, C5.1, D3.1, U1.11, U2.8
unnamed: C2.2, C4.2, C6.2, D4.2, MIX1.1, R16.1, U1.6, U2.4
unnamed: CVATTN1.1, D3.2, J5.9, J5.10, MIX1.3, R14.2
unnamed: CVATTN1.2, R3.1
unnamed: CV.1, CVATTN1.3
unnamed: D1.1, R11.2
unnamed: D1.2, R9.2, R10.1, U2.1
unnamed: D2.1, R12.2
unnamed: D2.2, R13.2, U2.7
unnamed: D4.1, J5.1, J5.2
unnamed: OSC1.1, R1.1
unnamed: OSC2.1, R2.1
unnamed: OUT.1, R17.2
unnamed: MIX1.2, R4.1
unnamed: R1.2, R6.2, U1.3
unnamed: R2.2, R5.2, U1.14
unnamed: R3.2, R4.2, R9.1, U2.2
unnamed: R7.2, U1.4
unnamed: R8.2, U1.13
unnamed: R10.2, R13.1, U2.6
unnamed: R11.1, U1.1
unnamed: R12.1, U1.16
unnamed: R14.1, R15.2, U1.5, U1.7, U1.12
unnamed: R16.2, R17.1, U1.8
